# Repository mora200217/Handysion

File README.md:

# Handysion 
_HandTracking Sensor Fusion System_

Handysion, is a JS Leap Motion Sensor Fusion, using Mediapipe Hand tracking system to expand the possible hand gestures. It allows to identify overlaping complex hand positions impossible to detect only with the Leap motion (LM) system. It basically takes the computer's frontal camera, to __estimate__ the hand key points distribution, and fuse them with the LM data. 

> This repository includes the documentation, and source code for Handysion, our __Sensors and Actuator Final Project__ at Universidad Nacional de Colombia - Sede Bogotá 

## Startup-Guide 
To begin using Handyion, clone the repository and install the JS dependencies. At project root, run: 
```
$ npm install
```
To run the dev server, run
```
$ npm run start 
```

## Understanding the code 
Basically, we are making a sensor fusion routine, with both datasets; LeapMotions and Hand Mediapipe Hand models. What is the problem we are trying to solve? Whe 
### Leap Motion 
### Mediapipe 

## Implementation 
The base web app is build on ReactJS, a frontend JS framework. It allows us to bundle all the dependencies in a depmap, avoiding comple imports for separate source codes.

## Sources 
* Mediapipe: https://google.github.io/mediapipe/solutions/hands
* LeapMotion: https://www.ultraleap.com

### Authors
- Valentina Hernández Montes (vahernandezmo@unal.edu.co)
- Andrés Mauricio Morales Martínez (amoralesma@unal.edu.co)

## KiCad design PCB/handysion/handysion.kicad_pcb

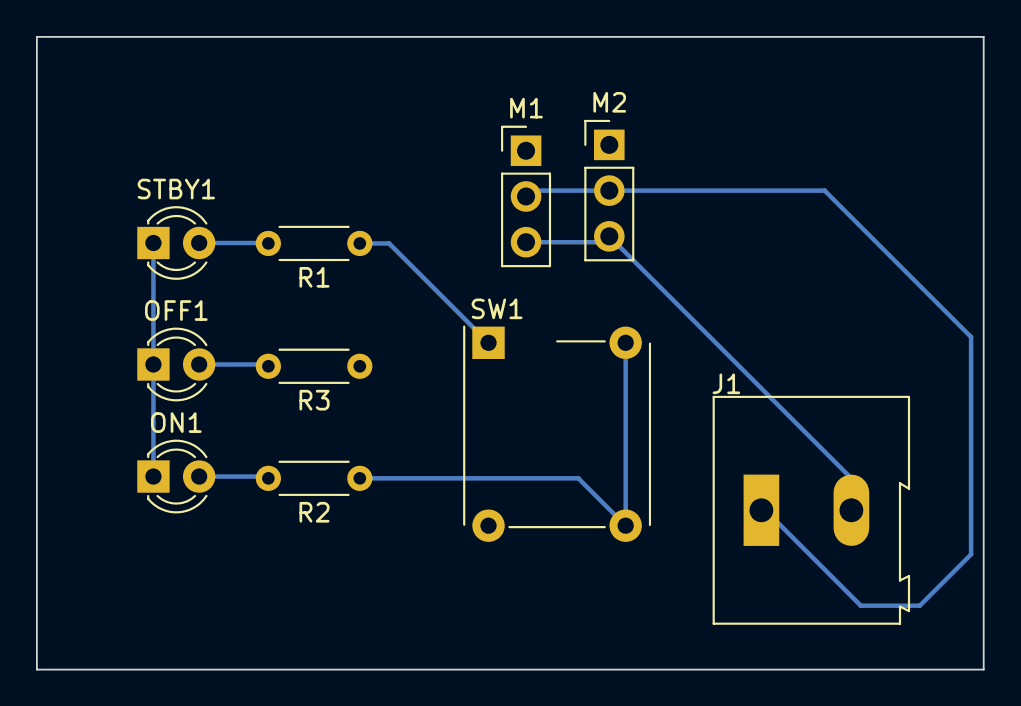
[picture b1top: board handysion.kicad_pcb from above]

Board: 2 copper layers, 52.6 x 35.2 mm, 10 parts (0 on the bottom side), 7 nets.

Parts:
J1: Screw_Terminal_01x02; TerminalBlock_Altech_AK300-2_P5.00mm
M1: Roll; PinHeader_1x03_P2.54mm_Vertical
M2: Pitch; PinHeader_1x03_P2.54mm_Vertical
OFF1: LED; LED_D3.0mm
ON1: LED; LED_D3.0mm
R1, R2, R3: 330; R_Axial_DIN0204_L3.6mm_D1.6mm_P5.08mm_Horizontal
STBY1: LED; LED_D3.0mm
SW1: SW_DP3T; SW_MEC_5GTH9

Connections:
+5V: J1.1, M1.2 (+), M2.2 (+)
GND: J1.2, M1.3 (-), M2.3 (-), OFF1.1 (K), ON1.1 (K), STBY1.1 (K)
unnamed: OFF1.2 (A), R3.2
unnamed: ON1.2 (A), R2.2
unnamed: R1.2, STBY1.2 (A)
ON: R1.1, SW1.1
STBY: R2.1, SW1.2

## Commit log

2022-12-06 [New] gitignore
2022-12-06 Update Readme. [Temporal Changes]
2022-12-06 [New] npm package
2022-12-06 [New] base config
2022-12-06 [Installed] leapjs v1.1.0
2022-12-06 [Done] LeapMotion Lecture
2022-12-06 [New] Basic GUI with title, bg and frame rate for LM
2022-12-06 [New] Three js source. Can import
2022-12-06 [Test] New Cube functional. Live example Three JS
2022-12-07 [New] Grid, animation and GUI orientation cube
2022-12-07 [Update] Create Visible GUI and rotative planegrid with orientation Cube
2022-12-07 [New] Leap Motion controller and Hand recognition
2022-12-07 [Update] Title Control platform
2022-12-07 [Update] Cube Pose emulates Hand. (Only for 1 Hand). No organized.
2022-12-07 React
2022-12-07 [Update] No direct import of LeapJs lib
2022-12-07 [Update] Readapt code to react. All in src
2022-12-07 [Update] Explain react startup
2022-12-07 [Update] Leberynth Mesh Added
2022-12-08 Conexión con WebSocket entre ESP31 (servidor) y PC (Cliente)
2022-12-08 [New] DXF for laser Cut
2022-12-08 [New] Kicad project
2022-12-08 [New] Fabrication Folder. DXF files and STL for 3D printing
2022-12-08 [Update] Added Kicad file ignore
2022-12-08 [New] Added images for documentation
2022-12-08 [Update] fusion image added
2022-12-09 [New] Transition with/without hand present
2022-12-09 [New] React bootstrap
2022-12-09 [New] Modal for disconnection user advice
2022-12-09 [Update] WS connection and angle transfer
2022-12-09 [Update] Image for disconnection advice
